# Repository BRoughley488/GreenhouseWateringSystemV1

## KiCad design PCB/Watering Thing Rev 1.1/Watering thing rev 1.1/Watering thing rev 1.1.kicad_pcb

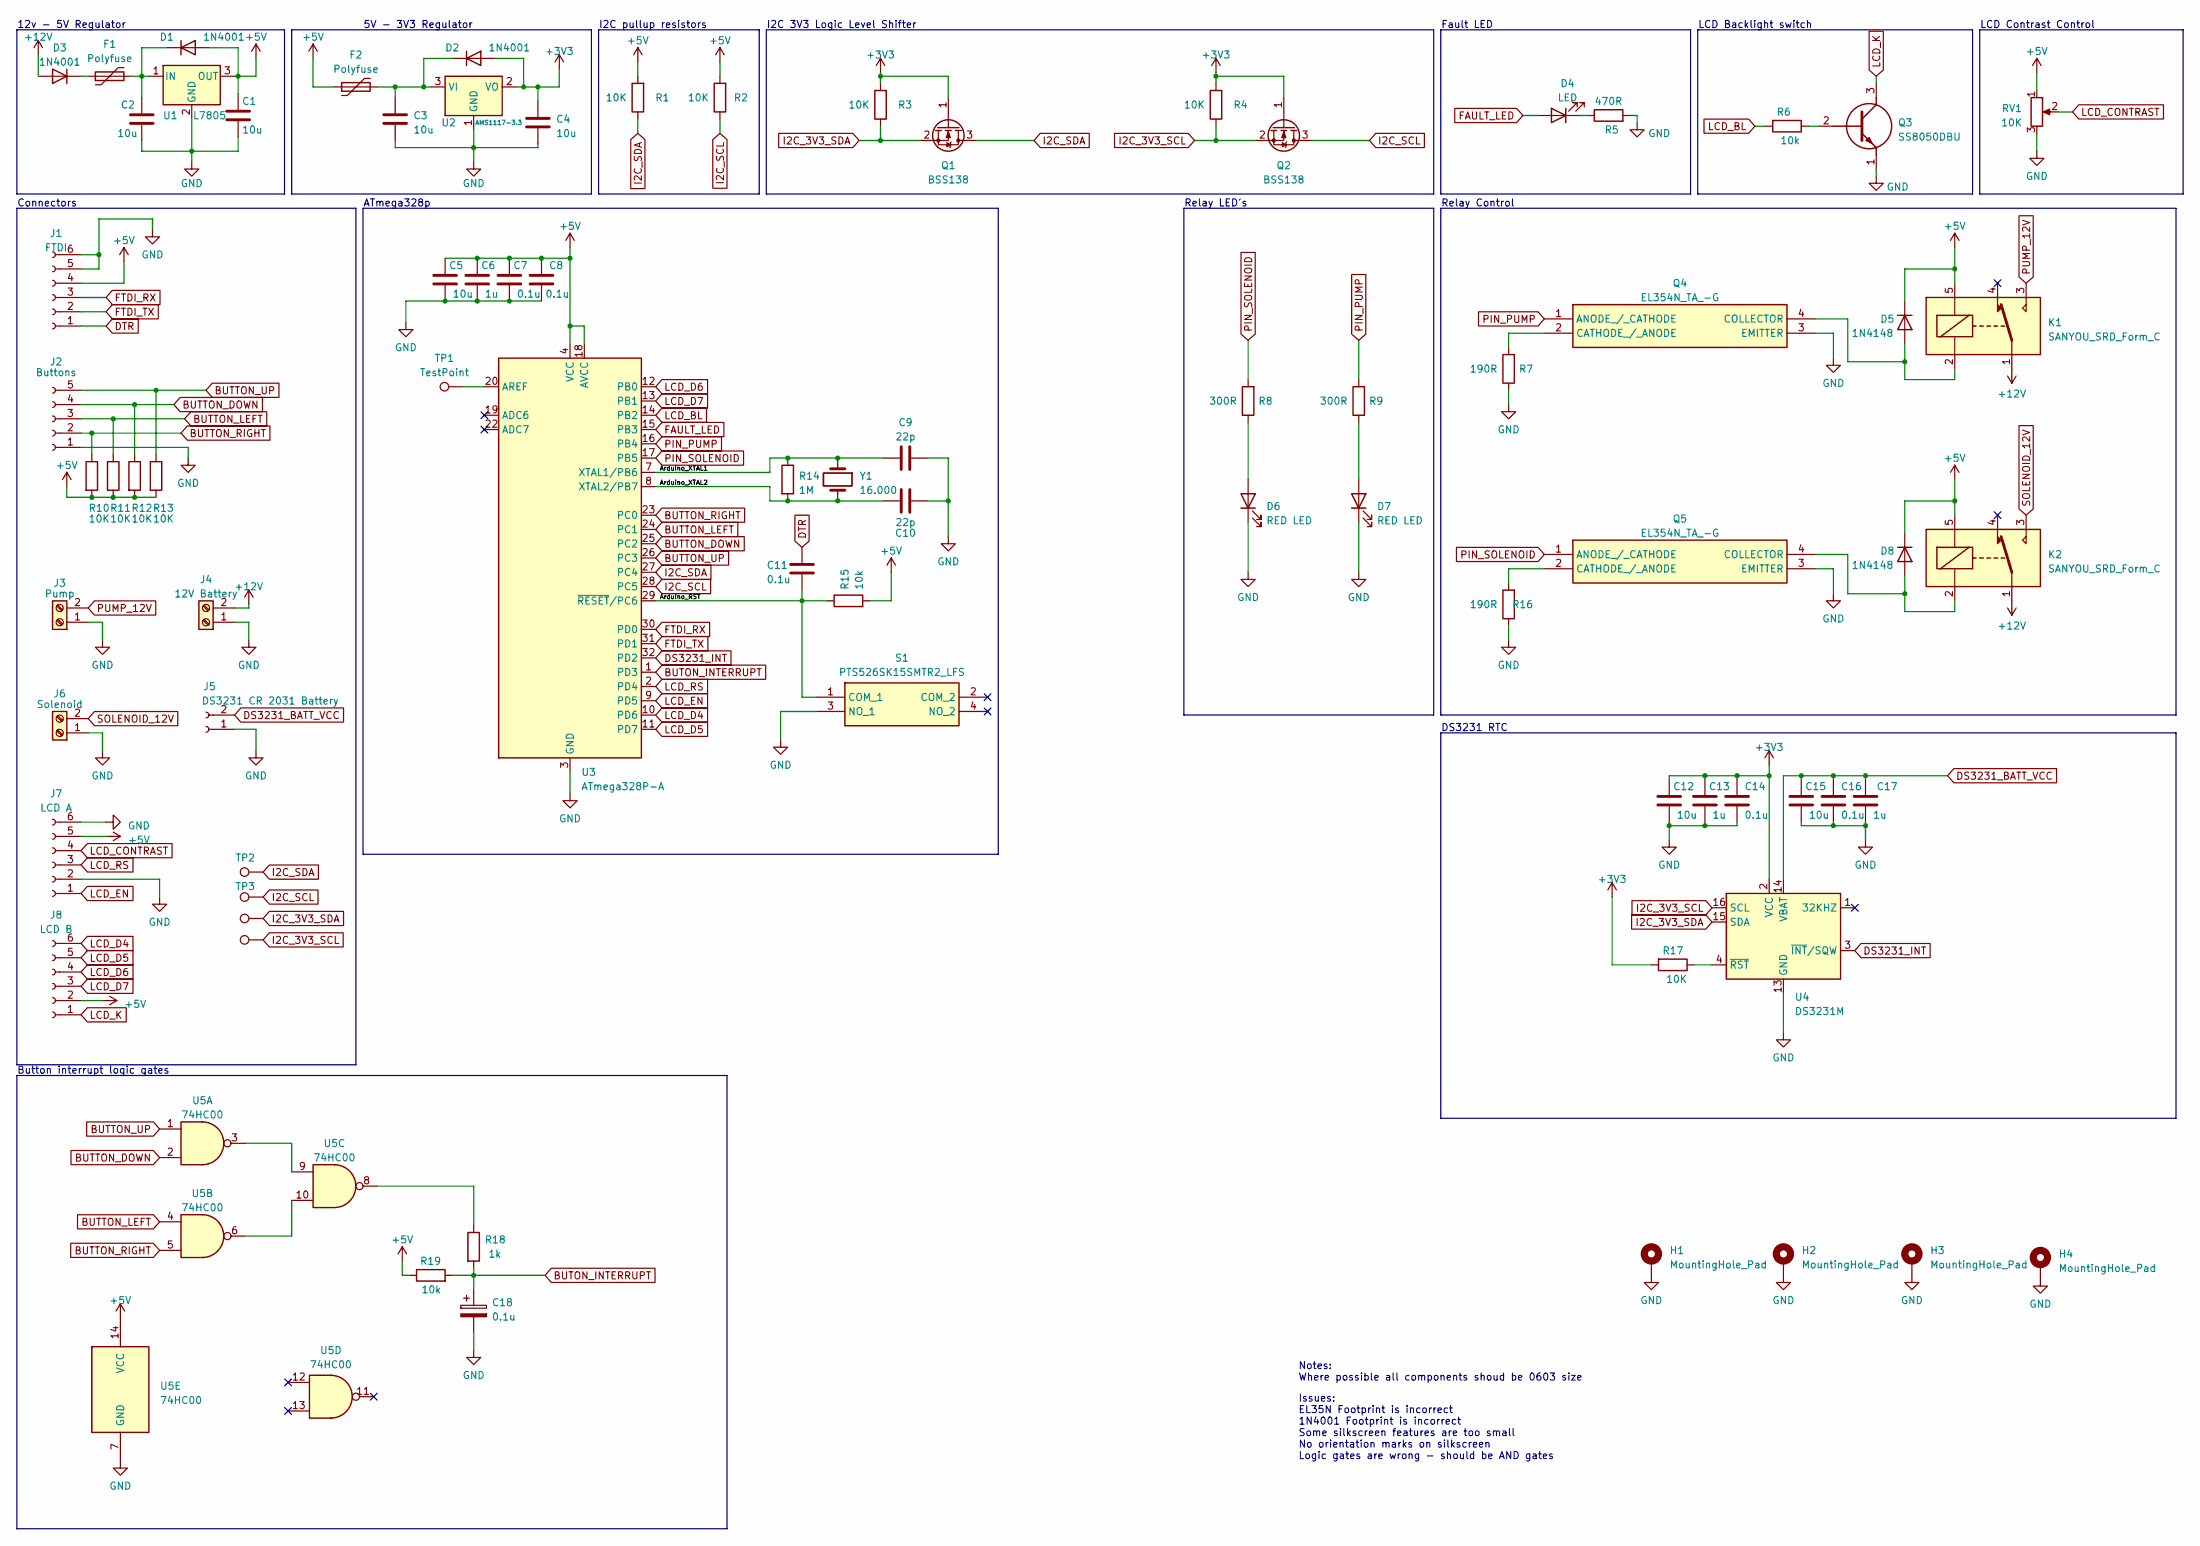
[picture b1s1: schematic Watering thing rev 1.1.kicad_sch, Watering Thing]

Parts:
C1, C2, C3, C4, C5, C12, C15: 10u; C_0603_1608Metric
C6, C13, C17: 1u; C_0603_1608Metric
C7, C8, C11, C14, C16, C18: 0.1u; C_0603_1608Metric
C9, C10: 22p; C_0603_1608Metric
D1, D2, D3: 1N4001; D_SOD-123
D4: LED; LED_0603_1608Metric
D5, D8: 1N4148; D_SOD-123
D6, D7: RED LED; LED_0603_1608Metric
F1, F2: Polyfuse; Fuse_0603_1608Metric
H1, H2, H3, H4: MountingHole_Pad; MountingHole_3.2mm_M3_DIN965_Pad_TopOnly
J1: FTDI; PinHeader_1x06_P2.54mm_Vertical
J2: Buttons; PinHeader_1x05_P2.54mm_Vertical
J3: Pump; TerminalBlock_Phoenix_PT-1,5-2-5.0-H_1x02_P5.00mm_Horizontal
J4: 12V Battery; TerminalBlock_Phoenix_PT-1,5-2-5.0-H_1x02_P5.00mm_Horizontal
J5: DS3231 CR 2031 Battery; TestPoint_2Pads_Pitch2.54mm_Drill0.8mm
J6: Solenoid; TerminalBlock_Phoenix_PT-1,5-2-5.0-H_1x02_P5.00mm_Horizontal
J7: LCD A; PinSocket_1x06_P2.54mm_Vertical
J8: LCD B; PinSocket_1x06_P2.54mm_Vertical
K1, K2: SANYOU_SRD_Form_C; Relay_SPDT_SANYOU_SRD_Series_Form_C
Q1, Q2: BSS138; SOT-23
Q3: SS8050DBU; TO-92Flat; Mouser Part Number 512-SS8050DBU
Q4, Q5: EL354N_TA_-G; SOP-4_3.8x4.1mm_P2.54mm; Manufacturer_Part_Number EL354N(TA)-G
R1, R2, R3, R4, R10, R11, R12, R13, R17: 10K; R_0603_1608Metric
R5: 470R; R_0603_1608Metric
R6, R15, R19: 10k; R_0603_1608Metric
R7, R16: 190R; R_0603_1608Metric
R8, R9: 300R; R_0603_1608Metric
R14: 1M; R_0603_1608Metric
R18: 1k; R_0603_1608Metric
RV1: 10K; Potentiometer_Runtron_RM-063_Horizontal
S1: PTS526SK15SMTR2_LFS; PTS526SK15SMTR2LFS; Mouser Part Number 611-PTS526SK15SMR2L
TP1, TP2, TP3, TP4, TP5: TestPoint; TestPoint_THTPad_D2.0mm_Drill1.0mm
U1: L7805; TO-220-3_Vertical
U2: AMS1117-3.3; SOT-223-3_TabPin2
U3: ATmega328P-A; TQFP-32_7x7mm_P0.8mm
U4: DS3231M; SOIC-16W_7.5x10.3mm_P1.27mm
U5: 74HC00; SOIC-14_3.9x8.7mm_P1.27mm
Y1: 16.000; Crystal_HC18-U_Vertical

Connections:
+3V3: C4.1, C12.1, C13.1, C14.1, D2.2 (A), Q1.1 (G), Q2.1 (G), R3.2, R4.2, R17.2, U2.2 (VO), U4.2 (VCC)
+5V: C1.1, C5.1, C6.1, C7.1, C8.1, D1.2 (A), D5.1 (K), D8.1 (K), F2.1, J1.4, J7.5, J8.2, K1.5, K2.5, R1.2, R2.2, R10.2, R11.2, R12.2, R13.2, R15.2, R19.1, RV1.1, U1.3 (OUT), U3.4 (VCC), U3.6 (VCC), U3.18 (AVCC), U5.14 (VCC)
+12V: D3.2 (A), J4.2, K1.1, K2.1
/Arduino_RST: C11.1, R15.1, S1.1 (COM_1), U3.29 (~RESET/PC6)
/Arduino_XTAL1: C9.1, R14.1, U3.7 (XTAL1/PB6), Y1.1
/Arduino_XTAL2: C10.1, R14.2, U3.8 (XTAL2/PB7), Y1.2
BUTON_INTERRUPT: C18.1, R18.2, R19.2, U3.1 (PD3)
BUTTON_DOWN: J2.4, R12.1, U3.25 (PC2), U5.2
BUTTON_LEFT: J2.3, R11.1, U3.24 (PC1), U5.4
BUTTON_RIGHT: J2.2, R10.1, U3.23 (PC0), U5.5
BUTTON_UP: J2.5, R13.1, U3.26 (PC3), U5.1
DS3231_BATT_VCC: C15.1, C16.1, C17.1, J5.2, U4.14 (VBAT)
DS3231_INT: U3.32 (PD2), U4.3 (~INT/SQW)
DTR: C11.2, J1.1
FAULT_LED: D4.2 (A), U3.15 (PB3)
FTDI_RX: J1.3, U3.30 (PD0)
FTDI_TX: J1.2, U3.31 (PD1)
GND: C1.2, C2.2, C3.2, C4.2, C5.2, C6.2, C7.2, C8.2, C9.2, C10.2, C12.2, C13.2, C14.2, C15.2, C16.2, C17.2, C18.2, D6.1 (K), D7.1 (K), H1.1, H2.1, H3.1, H4.1, J1.5, J1.6, J2.1, J3.1, J4.1, J5.1, J6.1, J7.2, J7.6, Q3.1 (E), Q4.3 (EMITTER), Q5.3 (EMITTER), R5.2, R7.1, R16.1, RV1.3, S1.3 (NO_1), U1.2 (GND), U2.1 (GND), U3.3 (GND), U3.5 (GND), U3.21 (GND), U4.5 (GND), U4.6 (GND), U4.7 (GND), U4.8 (GND), U4.9 (GND), U4.10 (GND), U4.11 (GND), U4.12 (GND), U4.13 (GND), U5.7 (GND)
I2C_3V3_SCL: Q2.2 (S), R4.1, TP5.1, U4.16 (SCL)
I2C_3V3_SDA: Q1.2 (S), R3.1, TP4.1, U4.15 (SDA)
I2C_SCL: Q2.3 (D), R2.1, TP3.1, U3.28 (PC5)
I2C_SDA: Q1.3 (D), R1.1, TP2.1, U3.27 (PC4)
LCD_BL: R6.2, U3.14 (PB2)
LCD_CONTRAST: J7.4, RV1.2
LCD_D4: J8.6, U3.10 (PD6)
LCD_D5: J8.5, U3.11 (PD7)
LCD_D6: J8.4, U3.12 (PB0)
LCD_D7: J8.3, U3.13 (PB1)
LCD_EN: J7.1, U3.9 (PD5)
LCD_K: J8.1, Q3.3 (C)
LCD_RS: J7.3, U3.2 (PD4)
unnamed: C2.1, D1.1 (K), F1.2, U1.1 (IN)
unnamed: C3.1, D2.1 (K), F2.2, U2.3 (VI)
unnamed: D3.1 (K), F1.1
unnamed: D4.1 (K), R5.1
unnamed: D5.2 (A), K1.2, Q4.4 (COLLECTOR)
unnamed: D6.2 (A), R8.1
unnamed: D7.2 (A), R9.1
unnamed: D8.2 (A), K2.2, Q5.4 (COLLECTOR)
unnamed: Q3.2 (B), R6.1
unnamed: Q4.2 (CATHODE_/_ANODE), R7.2
unnamed: Q5.2 (CATHODE_/_ANODE), R16.2
unnamed: R18.1, U5.8
unnamed: TP1.1, U3.20 (AREF)
unnamed: R17.1, U4.4 (~RST)
unnamed: U5.3, U5.9
unnamed: U5.6, U5.10
PIN_PUMP: Q4.1 (ANODE_/_CATHODE), R9.2, U3.16 (PB4)
PIN_SOLENOID: Q5.1 (ANODE_/_CATHODE), R8.2, U3.17 (PB5)
PUMP_12V: J3.2, K1.3
SOLENOID_12V: J6.2, K2.3

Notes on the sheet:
Relay LED's
5V - 3V3 Regulator
Fault LED
Relay Control
Connectors
LCD Contrast Control
DS3231 RTC
12v - 5V Regulator
ATmega328p
LCD Backlight switch
Issues: EL35N Footprint is incorrect 1N4001 Footprint is incorrect Some silkscreen features are too small No orientation marks on silkscreen Logic gates are wrong - should be AND gates
Notes: Where possible all components shoud be 0603 size
I2C 3V3 Logic Level Shifter
Button interrupt logic gates
I2C pullup resistors

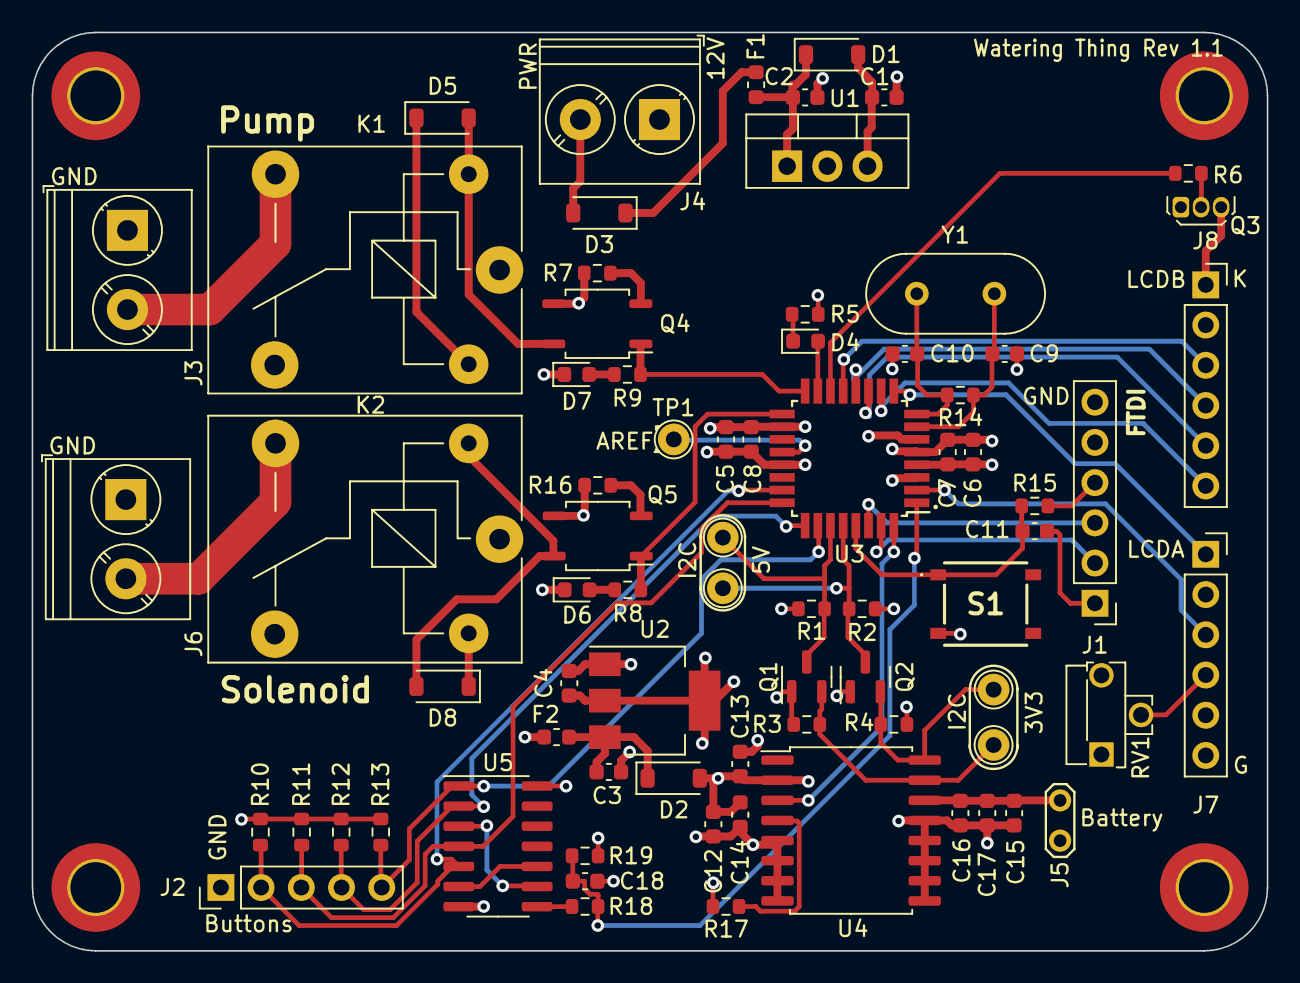
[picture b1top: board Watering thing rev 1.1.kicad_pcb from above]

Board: 4 copper layers, 78.0 x 58.0 mm, 79 parts (0 on the bottom side), 51 nets.

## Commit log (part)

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2025-02-24 testing the soutce control????
2025-02-24 added logic to turn solenoid / pump on and off, along with the wait for the pump to finish
2025-02-24 added EEPROM read and write functions
2025-02-24 fsasfdfafa
2025-02-24 added UI elements for water low state
2025-02-25 Added code for setting the next alarm
2025-03-06 added loads, it all works now
